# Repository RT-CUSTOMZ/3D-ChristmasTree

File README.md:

A 3D Christmas Tree based on WLED
USE WS2812 or SK6812 LEDs in combination with an WaveShare ESP32-S3 Mini Development Board
https://eckstein-shop.de/WaveShare-ESP32-S3-Mini-Development-Board-ESP32-S3FH4R2-240MHz-24GHz-Wi-Fi-Bluetooth-5

Board thickness 1.6 mm
Can use HASL or chem. Gold plating for silver or gold colored christmas ornaments

Populate boards accoring to silk screen prints
Connectors belong to the side with the silk screen print
Check LED function before assambling the tree
Slide the two tree PCBs into each other and use symbols on PCBs to ensure correct orientation
Afterwards use the same symbols as solder joints to give the tree more stability
Lastely connect the brain PCB to the tree assembly

As of end 2024 the WLED software is marked experimental for ESP32-S3 chipset, therefore install WLED via 
https://wled-install.github.io/
and select an ESP32-S3 version (4 MB Flash).

After installation open WLED controls and load Presets and Configuration from Backup Files

Short button press - On / Off
Long button press - Toggle presets

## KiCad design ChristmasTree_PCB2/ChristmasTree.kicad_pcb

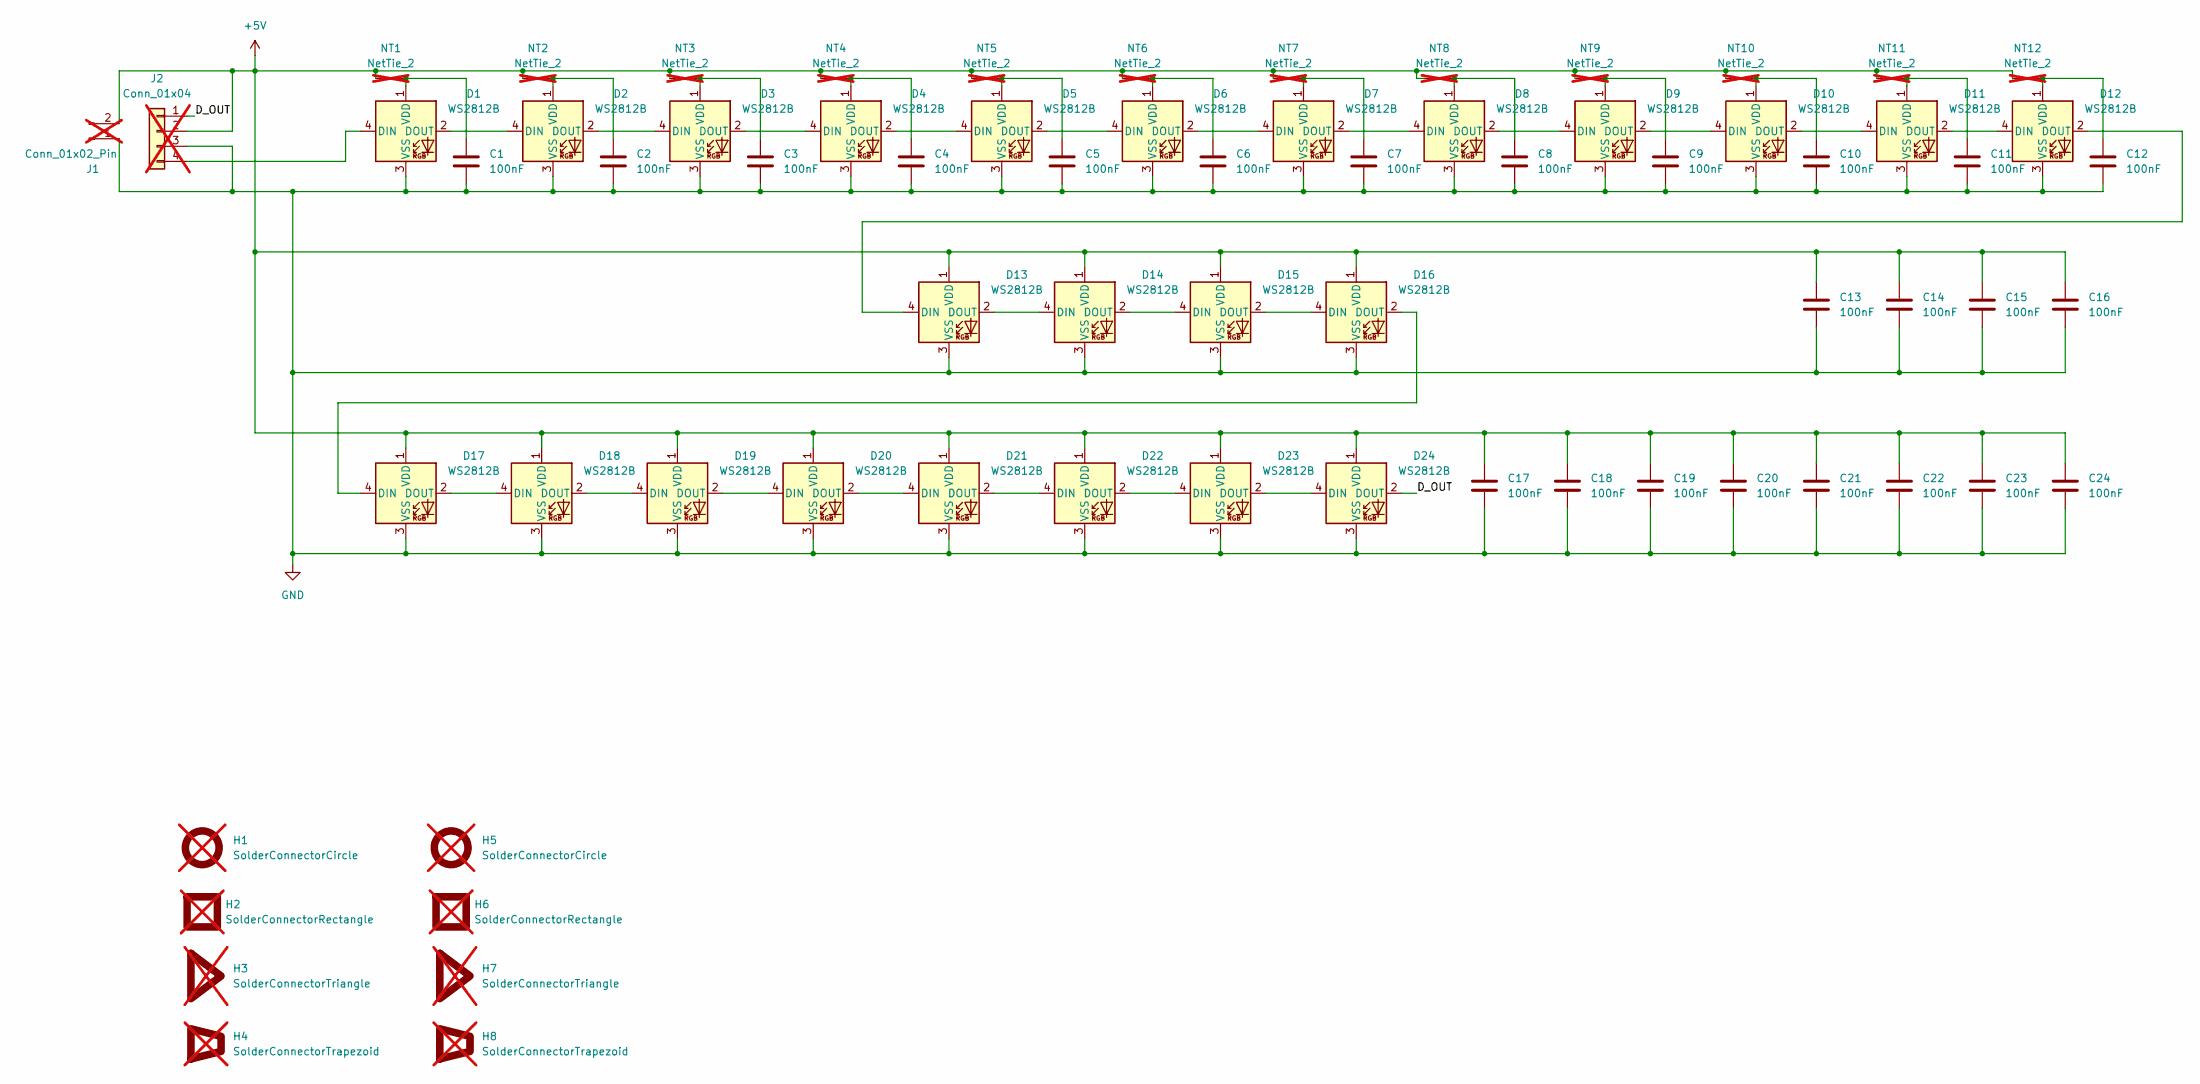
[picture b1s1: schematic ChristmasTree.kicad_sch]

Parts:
C1, C2, C3, C4, C5, C6, C7, C8, C9, C10, C11, C12, C13, C14, C15, C16, C17, C18, C19, C20, C21, C22, C23, C24: 100nF; C_0805_2012Metric_Pad1.18x1.45mm_HandSolder; LCSC C396718
D1, D2, D3, D4, D5, D6, D7, D8, D9, D10, D11, D12: WS2812B; LED_WS2812B_PLCC4_ECO1; LCSC C5378724
D13, D14, D15, D16, D17, D18, D19, D20, D21, D22, D23, D24: WS2812B; LED_WS2812B_ECO2; LCSC C5378724
H1, H5: SolderConnectorCircle; not fitted
H2, H6: SolderConnectorRectangle; not fitted
H3, H7: SolderConnectorTriangle; not fitted
H4, H8: SolderConnectorTrapezoid; not fitted
J1: Conn_01x02_Pin; PinHeader_1x02_P2.54mm_Horizontal; not fitted
J2: Conn_01x04; PinHeader_1x04_P2.54mm_Horizontal; not fitted
NT1, NT2, NT3, NT4, NT5, NT6, NT7, NT8, NT9, NT10, NT11, NT12: NetTie_2; NetTie-2_SMD_Pad0.5mm; not fitted

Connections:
+5V: C13.1, C14.1, C15.1, C16.1, C17.1, C18.1, C19.1, C20.1, C21.1, C22.1, C23.1, C24.1, D13.1 (VDD), D14.1 (VDD), D15.1 (VDD), D16.1 (VDD), D17.1 (VDD), D18.1 (VDD), D19.1 (VDD), D20.1 (VDD), D21.1 (VDD), D22.1 (VDD), D23.1 (VDD), D24.1 (VDD), J1.2, J2.2, NT1.1, NT2.1, NT3.1, NT4.1, NT5.1, NT6.1, NT7.1, NT8.1, NT9.1, NT10.1, NT11.1, NT12.1
/D_OUT: D24.2 (DOUT), J2.1
GND: C1.2, C2.2, C3.2, C4.2, C5.2, C6.2, C7.2, C8.2, C9.2, C10.2, C11.2, C12.2, C13.2, C14.2, C15.2, C16.2, C17.2, C18.2, C19.2, C20.2, C21.2, C22.2, C23.2, C24.2, D1.3 (VSS), D2.3 (VSS), D3.3 (VSS), D4.3 (VSS), D5.3 (VSS), D6.3 (VSS), D7.3 (VSS), D8.3 (VSS), D9.3 (VSS), D10.3 (VSS), D11.3 (VSS), D12.3 (VSS), D13.3 (VSS), D14.3 (VSS), D15.3 (VSS), D16.3 (VSS), D17.3 (VSS), D18.3 (VSS), D19.3 (VSS), D20.3 (VSS), D21.3 (VSS), D22.3 (VSS), D23.3 (VSS), D24.3 (VSS), J1.1, J2.3
unnamed: D1.4 (DIN), J2.4
unnamed: D1.2 (DOUT), D2.4 (DIN)
unnamed: C1.1, D1.1 (VDD), NT1.2
unnamed: D2.2 (DOUT), D3.4 (DIN)
unnamed: C2.1, D2.1 (VDD), NT2.2
unnamed: D3.2 (DOUT), D4.4 (DIN)
unnamed: C3.1, D3.1 (VDD), NT3.2
unnamed: D4.2 (DOUT), D5.4 (DIN)
unnamed: C4.1, D4.1 (VDD), NT4.2
unnamed: D5.2 (DOUT), D6.4 (DIN)
unnamed: C5.1, D5.1 (VDD), NT5.2
unnamed: D6.2 (DOUT), D7.4 (DIN)
unnamed: C6.1, D6.1 (VDD), NT6.2
unnamed: D7.2 (DOUT), D8.4 (DIN)
unnamed: C7.1, D7.1 (VDD), NT7.2
unnamed: D8.2 (DOUT), D9.4 (DIN)
unnamed: C8.1, D8.1 (VDD), NT8.2
unnamed: C9.1, D9.1 (VDD), NT9.2
unnamed: D9.2 (DOUT), D10.4 (DIN)
unnamed: D10.2 (DOUT), D11.4 (DIN)
unnamed: C10.1, D10.1 (VDD), NT10.2
unnamed: D11.2 (DOUT), D12.4 (DIN)
unnamed: C11.1, D11.1 (VDD), NT11.2
unnamed: D12.2 (DOUT), D13.4 (DIN)
unnamed: C12.1, D12.1 (VDD), NT12.2
unnamed: D13.2 (DOUT), D14.4 (DIN)
unnamed: D14.2 (DOUT), D15.4 (DIN)
unnamed: D15.2 (DOUT), D16.4 (DIN)
unnamed: D16.2 (DOUT), D17.4 (DIN)
unnamed: D17.2 (DOUT), D18.4 (DIN)
unnamed: D18.2 (DOUT), D19.4 (DIN)
unnamed: D19.2 (DOUT), D20.4 (DIN)
unnamed: D20.2 (DOUT), D21.4 (DIN)
unnamed: D21.2 (DOUT), D22.4 (DIN)
unnamed: D22.2 (DOUT), D23.4 (DIN)
unnamed: D23.2 (DOUT), D24.4 (DIN)

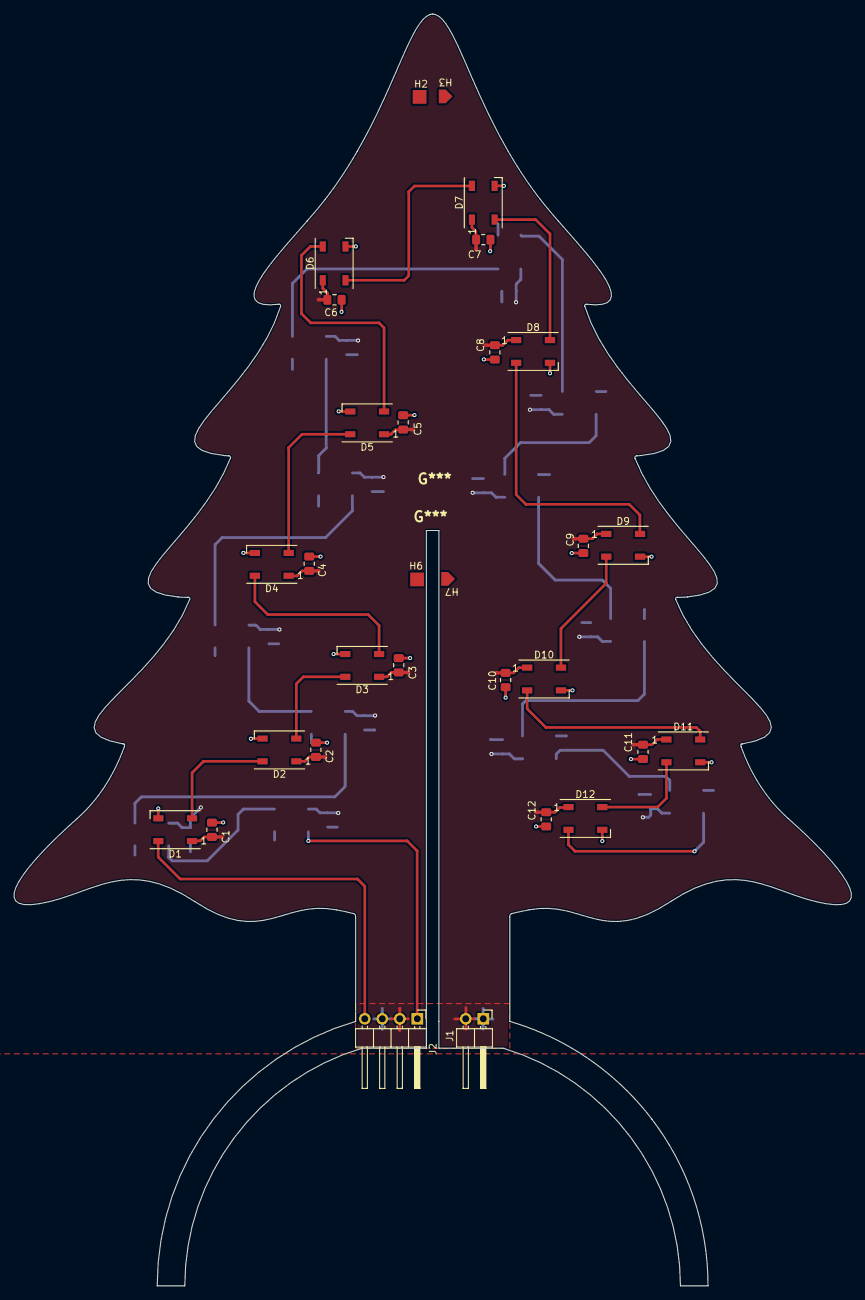
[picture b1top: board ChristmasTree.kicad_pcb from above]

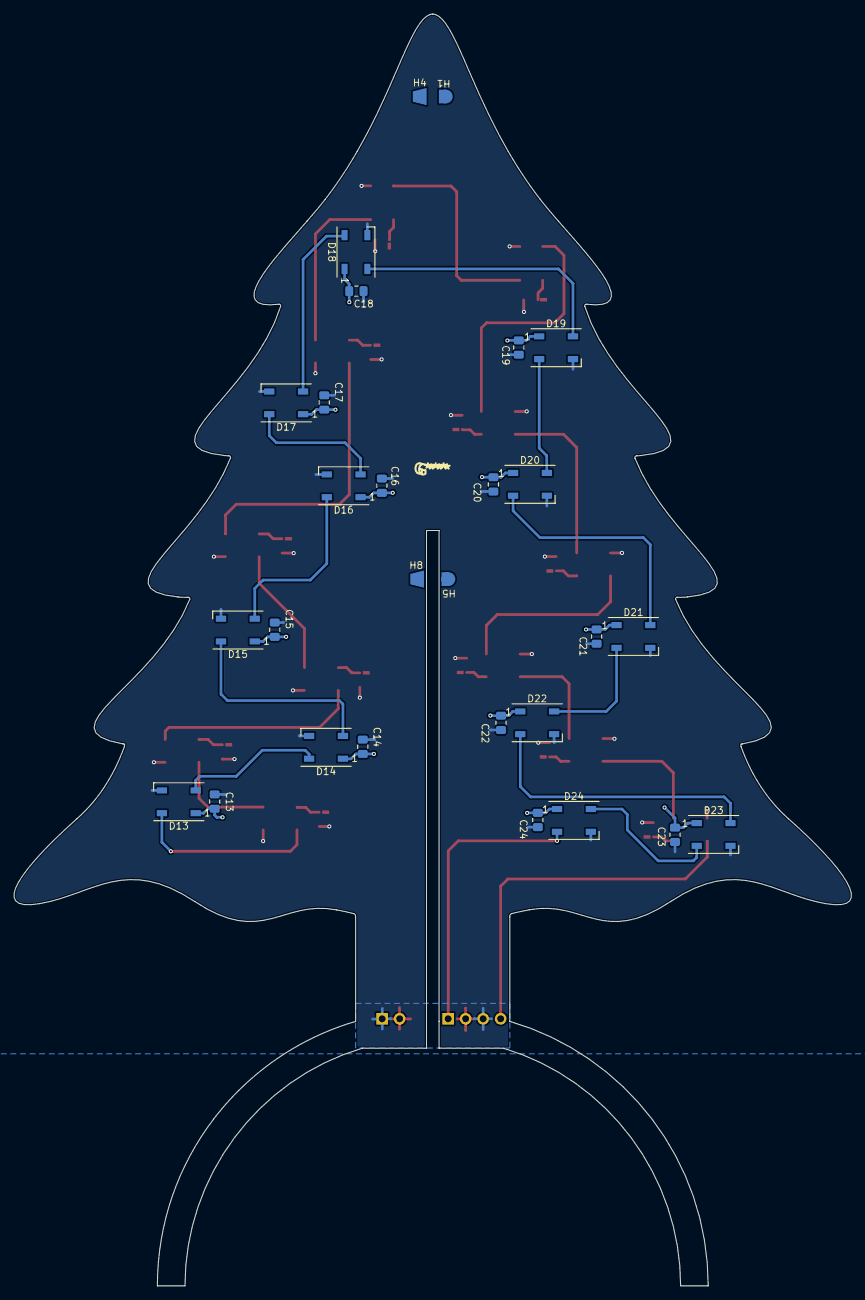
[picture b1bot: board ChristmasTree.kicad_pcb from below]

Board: 2 copper layers, 121.4 x 184.5 mm, 70 parts (28 on the bottom side), 39 nets.

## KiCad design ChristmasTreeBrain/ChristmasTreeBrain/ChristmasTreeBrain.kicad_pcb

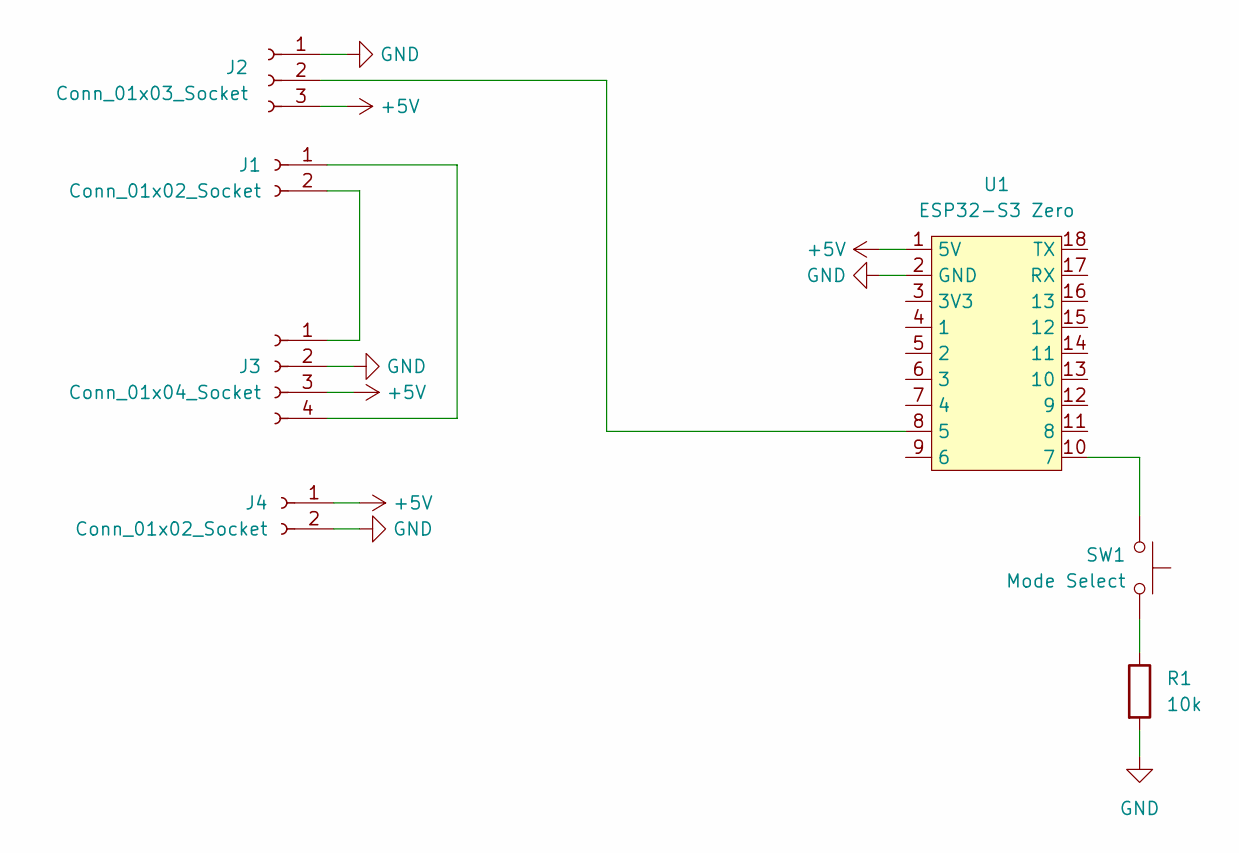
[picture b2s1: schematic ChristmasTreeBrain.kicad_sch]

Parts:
J1, J4: Conn_01x02_Socket; PinSocket_1x02_P2.54mm_Vertical
J2: Conn_01x03_Socket; PinSocket_1x03_P2.54mm_Vertical
J3: Conn_01x04_Socket; PinSocket_1x04_P2.54mm_Vertical
R1: 10k; R_0805_2012Metric
SW1: Mode Select; SW_Tactile_SPST_Angled_PTS645Vx83-2LFS
U1: ESP32-S3 Zero; ESP32-S3 Mini

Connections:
+5V: J2.3, J3.3, J4.1, U1.1 (5V)
GND: J2.1, J3.2, J4.2, R1.2, U1.2 (GND)
unnamed: J1.1, J3.4
unnamed: J1.2, J3.1
unnamed: J2.2, U1.8 (5)
unnamed: R1.1, SW1.1
unnamed: SW1.2, U1.10 (7)

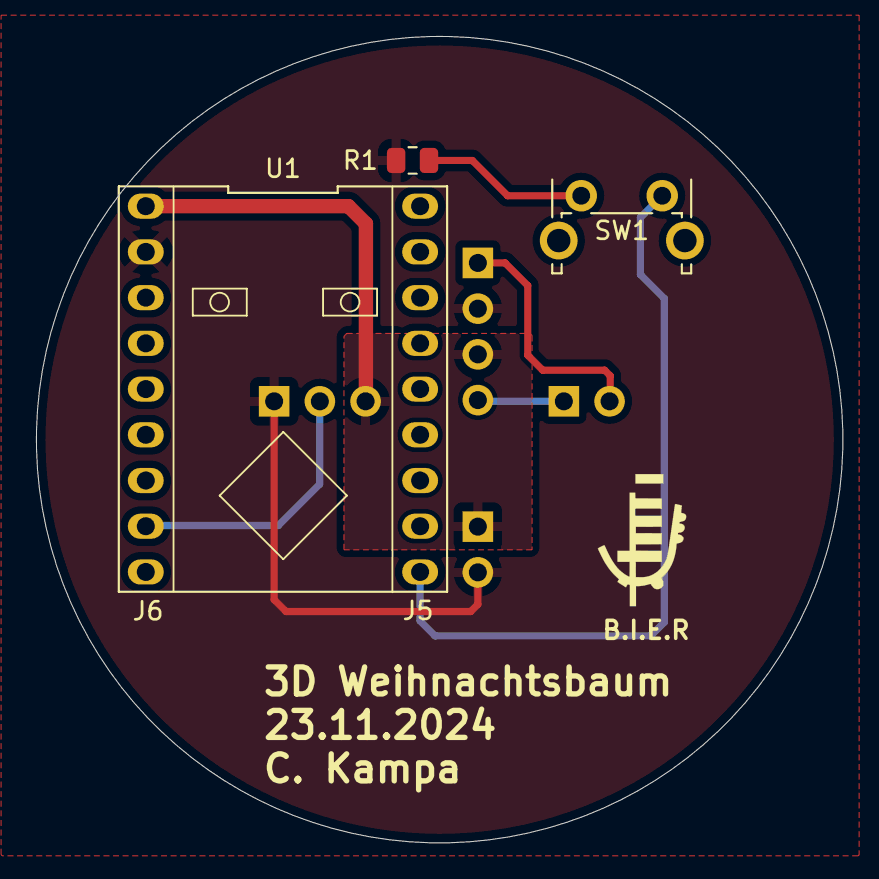
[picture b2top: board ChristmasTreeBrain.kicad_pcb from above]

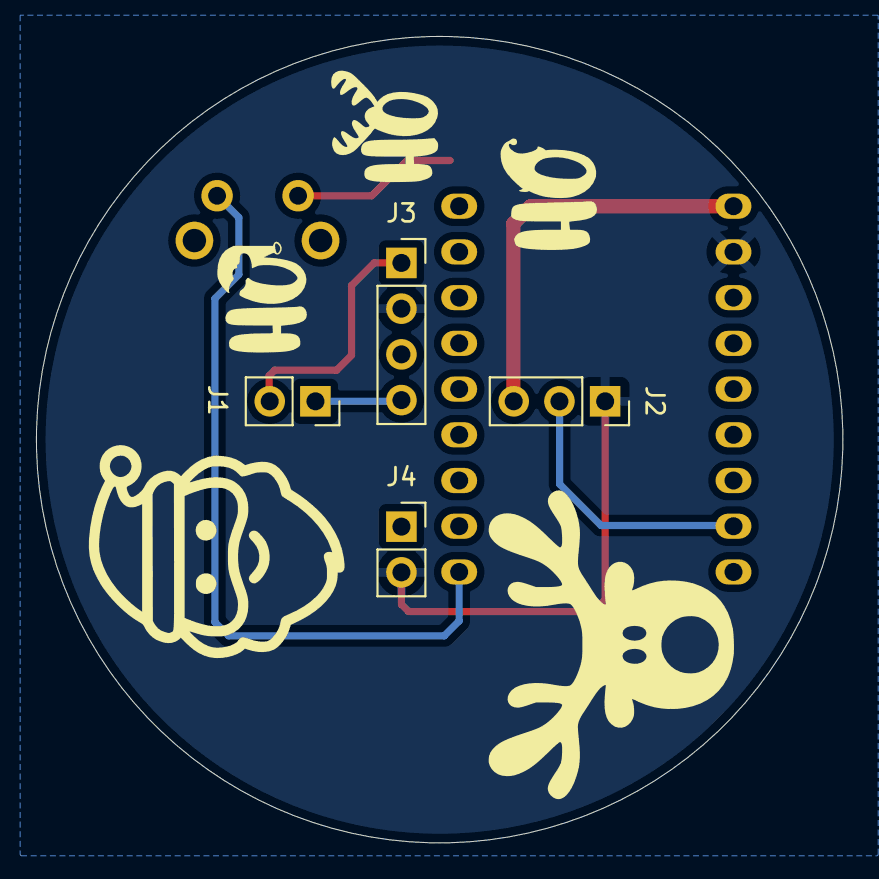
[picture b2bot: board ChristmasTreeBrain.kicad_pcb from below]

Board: 2 copper layers, 44.8 x 44.8 mm, 7 parts (4 on the bottom side), 7 nets.

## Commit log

2024-12-05 V1 für Wichteln 2024
2024-12-05 Footprints used for special silk screen prints
2024-12-05 Presets and Configuartion for 3D Tree
